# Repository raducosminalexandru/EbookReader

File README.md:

# OpenBook - E-book Reader Open-Source

In cadrul proiectului **OpenBook**, ne propunem sa revoluționam industria cititului digital prin dezvoltarea unui **e-book reader accesibil, eficient si open-source**. 🌍📚

Cu tehnologia de astazi, accesul la informatie este mai rapid ca niciodata, iar **OpenBook** isi propune sa ofere o solutie accesibila tuturor celor care doresc sa citeasca oriunde, oricand, fara a depinde de preturi exorbitante sau de platforme inchise. Suntem o echipa pasionata si inovativa, iar rolul nostru in acest proiect este sa creem un dispozitiv care sa ofere o experienta de citire excelenta si sa fie disponibil pentru toti utilizatorii, fara bariere. 💡

**OpenBook** este un e-book reader care va permite cititorilor sa acceseze si sa citeasca carti digitale intr-un mod simplu si eficient. Acesta ofera o solutie economica si open-source, ceea ce inseamna ca orice persoana va putea sa-l foloseasca, personalizeze sau imbunatateasca, fara restrictii legate de software sau costuri ridicate.

## Cum functioneaza

Prin utilizarea unor componente hardware eficiente si un software open-source, **OpenBook** va oferi o experienta de citire fluida, cu un design simplu si intuitiv. Acesta va suporta formate de carti populare si va fi usor de utilizat, chiar si pentru utilizatorii care nu sunt familiarizati cu tehnologia.

Prin intermediul acestui dispozitiv, punem bazele unui produs care va oferi cititorilor libertatea de a se bucura de carti digitale intr-un mod accesibil si fara compromisuri in ceea ce priveste performanta si functionalitatea.

## Bill of Materials (BOM) - varianta succinta a fisierului BOM

| Componenta               | Link si Datasheet                                                                                           |
|--------------------------|-------------------------------------------------------------------------------------------------------------|
| **ESP32-C6-WROOM-1-N8**   | [Mouser](https://eu.mouser.com/ProductDetail/Espressif-Systems/ESP32-C6-WROOM-1-N8?qs=8Wlm6%252BaMh8ST02Gmwp74cw%3D%3D) |
| **W25Q512JVEIQ**               | [Mouser](https://eu.mouser.com/ProductDetail/Winbond/W25Q512JVEIQ?qs=l7cgNqFNU1jw6svr3at6tA%3D%3D)                                             |
| **DS3231SN#**       | [Mouser](https://www.mouser.ro/ProductDetail/100uF-Capacitor](https://eu.mouser.com/ProductDetail/Analog-Devices-Maxim-Integrated/DS3231SN?qs=1eQvB6Dk1vhUlr8%2FOrV0Fw%3D%3D))                                         |
| **FH34SRJ-24S-0.5SH** | [Mouser](https://www.mouser.ro/ProductDetail/Atmel/ATMEGA328P](https://eu.mouser.com/ProductDetail/Hirose-Connector/FH34SRJ-24S-0.5SH50?qs=iyLo5FA4poC8fzWlavnA7A%3D%3D))                                     |
| **USB4110-GF-A** | [Mouser](https://www.mouser.ro/ProductDetail/Atmel/ATMEGA328P](https://eu.mouser.com/ProductDetail/Hirose-Connector/FH34SRJ-24S-0.5SH50?qs=iyLo5FA4poC8fzWlavnA7A%3D%3D)](https://eu.mouser.com/ProductDetail/GCT/USB4110-GF-A?qs=KUoIvG%2F9IlYiZvIXQjyJeA%3D%3D))                                     |
| **BME680** | [Mouser](https://www.mouser.ro/ProductDetail/Atmel/ATMEGA328P](https://eu.mouser.com/ProductDetail/Hirose-Connector/FH34SRJ-24S-0.5SH50?qs=iyLo5FA4poC8fzWlavnA7A%3D%3D)](https://eu.mouser.com/ProductDetail/GCT/USB4110-GF-A?qs=KUoIvG%2F9IlYiZvIXQjyJeA%3D%3D)](https://eu.mouser.com/ProductDetail/Bosch-Sensortec/BME680?qs=v271MhAjFHjo0yA%2FC4OnDQ%3D%3D))                                     |
| **XC6220A331MR-G** | [Mouser](https://eu.mouser.com/ProductDetail/Torex-Semiconductor/XC6220A331MR-G?qs=AsjdqWjXhJ8ZSWznL1J0gg%3D%3D)                                     |
| **USBLC6-2SC6Y** | [Mouser](https://ro.mouser.com/ProductDetail/STMicroelectronics/USBLC6-2SC6Y?qs=gNDSiZmRJS%2FOgDexvXkdow%3D%3D&_gl=1*hyv6ey*_ga*MTY0NzAzMzgwNi4xNzQyMDMzODgx*_ga_15W4STQT4T*MTc0MzA3NjI1Ny40LjEuMTc0MzA3NjMxMC43LjAuMA)                                     |
| **BD5229G-TR** | [Mouser](https://ro.mouser.com/ProductDetail/ROHM-Semiconductor/BD5229G-TR?qs=4kLU8WoGk0vvnhrrYwdszw%3D%3D)                                     |
| **MAX17048G+T10** | [Mouser](https://ro.mouser.com/ProductDetail/Analog-Devices-Maxim-Integrated/MAX17048G%2bT10?qs=D7PJwyCwLAoGnnn8jEPRBQ%3D%3D)                                     |
| **W25Q512JVEIQ** | [Mouser](https://ro.mouser.com/ProductDetail/ROHM-Semiconductor/BD5229G-TR?qs=4kLU8WoGk0vvnhrrYwdszw%3D%3D](https://ro.mouser.com/ProductDetail/Winbond/W25Q512JVEIQ?qs=l7cgNqFNU1jw6svr3at6tA%3D%3D))  
| **Qwiic Right Angle** | [Mouser](https://ro.mouser.com/ProductDetail/Adafruit/4208?qs=PzGy0jfpSMtbScLbr0L5dw%3D%3D) |

Urmatoarea imagine prezinta diagrama bloc de interconectare a componentelor, inclusiv tensiunile de alimentare si protocoalele de comunicatie utilizate intre ele. 🔌📡

<div align="center">

</div>

Modelul 3D al PCB-ului poate fi observat si in imaginea urmatoare, ceea ce permite o analiza detaliata a componentei si a configuratiei acestuia. Acest model ofera o perspectiva clara asupra dimensiunilor, plasarii componentelor si a traseelor de pe placa, ajutand la identificarea posibilelor interferente sau probleme de proiectare.

<div align="center">

</div>

Putem vizualiza si traseele mai bine in modelul 3D, ceea ce faciliteaza o analiza mai detaliata a conexiunilor dintre componente. Acest lucru permite identificarea eventualelor probleme legate de lungimea sau latimea traseelor, precum si a eventualelor puncte de coliziune sau interferenta.

<div align="center">

</div>

📐 **Integrarea modelului 3D al display-ului si al bateriei**

Pentru o reprezentare cat mai completa a ansamblului final, au fost incluse in proiect si modelele 3D ale display-ului si ale bateriei. Aceasta decizie a avut un rol esential in etapa de validare a designului, permitand o evaluare vizuala si functionala a intregului sistem, direct in mediul 3D.

Prin integrarea acestor componente, a fost posibila:
- ✅ **Verificarea compatibilitatii dimensionale** – Asigurarea ca fiecare componenta are un spatiu adecvat in interiorul carcasei, fara suprapuneri sau conflicte mecanice.
- 🧩 **Optimizarea pozitionarii componentelor** – Plasarea strategica a display-ului si bateriei pentru a facilita accesul, vizibilitatea, distributia greutatii si eficienta termica.
- 🧠 **Identificarea timpurie a potentialelor probleme de spatiu** – Vizualizarea in 3D permite observarea oricaror interferente sau nepotriviri intre PCB, baterie, display si carcasa proiectului.
- 🔧 **Eficientizarea procesului de prototipare** – Un model 3D complet si realist reduce riscul de erori in faza de fabricatie, scurtand ciclurile de testare si ajustare.

Aceasta abordare contribuie direct la cresterea fiabilitatii produsului final, asigurand ca toate componentele nu doar functioneaza impreuna, ci si se potrivesc perfect in structura fizica a dispozitivului.

</div>

<div align="center">

</div>

<div align="center">

</div>

<div align="center">

</div>

### Cerinte de 'Good Practice' respectate de dispozitiv:

✅ Traseele de alimentare (VCC, VUSB, VBUS, 3V3 etc.) sunt rutate folosind width = 0.3mm, semnalele de date cu minimum width de 0.15mm.  
✅ Antena modulului ESP32 este amplasata spre exteriorul PCB-ului si PCB-ul trebuie sa fie decupat sub antena.  
✅ Verificare ERC si DRC.  
✅ Condensatoarele de decuplare (100nF) sunt amplasate cat mai aproape de pinii de alimentare ai diferitelor module si circuite integrate.  
✅ Suprafata PCB-ului de sub antena modulului ESP32 a fost decupata pentru a crea cat mai putine interferente cu semnalul radio.  
✅ Planuri de masa situate pe ambele nivele (TOP, BOTTOM).  
✅ Antena modulului ESP32 este amplasata spre exteriorul PCB-ului si PCB-ul este decupat sub antena.  
✅ S-a aplicat 'Via Stitching' intre cele doua planuri de masa, in special in preajma modulului ESP32, precum si in jurul componentelor principale.
✅ Placa are grosimea de 1mm, lucru ce permite introducerea in carcasa si pozitionarea corecta a mufelor.
✅ Vias-uri legate de masa au fost aplicate in toate zonele in care nu se facea 'Pour'.
✅ Valorile rezistentelor si condensatoarelor au fost sterse din 'Board' de pe layer-ul 'Silkscreen' pentru a permite o lizibilitate mai buna.
✅ Footprint-urile anumitor componente au fost schimbate prin modificarea marimilor unor pini, permitand traseele de putere sa se lege la ele, acestea fiind mai groase.
✅ Nu exista unghiuri drepte in cadrul rutarii pe placa.

### Erori acceptate pe dispozitiv:
✅Erorile 'Board Outline Clearance', conform cerintelor impuse.

### 🌐 Surse auxiliare utilizate pentru modele 3D

## Surse externe pentru modelarea 3D a ansamblului

Pentru a completa designul 3D al placii si a asigura o reprezentare cat mai fidela a ansamblului, au fost utilizate urmatoarele surse externe:

🔍 **Component Search Engine**  
Aceasta platforma a fost principalul instrument folosit pentru importarea modelelor 3D ale componentelor electronice standard. A oferit o integrare rapida si precisa cu software-ul de proiectare, facilitand plasarea corecta a componentelor in layout-ul 3D.

🟢 **Farnell**  
Modelele 3D ale butoanelor nu erau disponibile in Component Search Engine, asa ca s-a apelat la biblioteca pusa la dispozitie de Farnell. Aceasta ofera fisiere 3D compatibile si bine detaliate, utile pentru verificarea dimensiunilor fizice si a spatiului ocupat pe placa.

📦 **GrabCAD**  
Modelul 3D al Solder Jumper-ului (SJ) a fost descarcat de pe GrabCAD, o platforma colaborativa care pune la dispozitie o varietate larga de modele CAD. A fost ales un model potrivit, care a fost ulterior ajustat pentru a corespunde dimensiunilor reale folosite in proiect.

# Pinii ESP32 C6 folositi

Se poate vizualiza modul de conectare al componentelor in raport cu ESP32 C6. Se poate observa clar cum acesta poate fi atat 'Master', cat si 'Slave', lucru ce permite comunicatia SPI.

## 1. SD Card
- **CLK** → GPIO6  
- **CMD** → GPIO7  
- **DATA0** → GPIO8  
- **DATA1** → GPIO9  
- **DATA2** → GPIO10  
- **DATA3** → GPIO11  

## 2. Ecran E-Paper
Comunicare prin SPI și GPIO-uri adiționale:
- **MOSI** → GPIO4  
- **SCK** → GPIO5  
- **DC** → GPIO18  
- **CS** → GPIO17  
- **BUSY** → GPIO16  
- **RESET** → GPIO15  

## 3. Memorie NOR Flash 64MB (W25Q512JV)
Comunicare prin SPI:
- **MOSI** → GPIO4  
- **MISO** → GPIO3  
- **CLK** → GPIO5  
- **CS** → GPIO2  

## 4. Senzor de mediu BME688 (I2C)
- **SCL** → GPIO20  
- **SDA** → GPIO19  

## 5. RTC DS3231SN (I2C)
- **SCL** → GPIO20  
- **SDA** → GPIO19  

## 6. Qwiic / Stemma QT (I2C)
- **SCL** → GPIO20  
- **SDA** → GPIO19  

## 7. Indicator nivel baterie (MAX17048G+T10) (I2C)
- **SCL** → GPIO20  
- **SDA** → GPIO19  

## 8. Buton de Reset și Boot
- **Reset** → GPIO0  
- **Boot** → GPIO1

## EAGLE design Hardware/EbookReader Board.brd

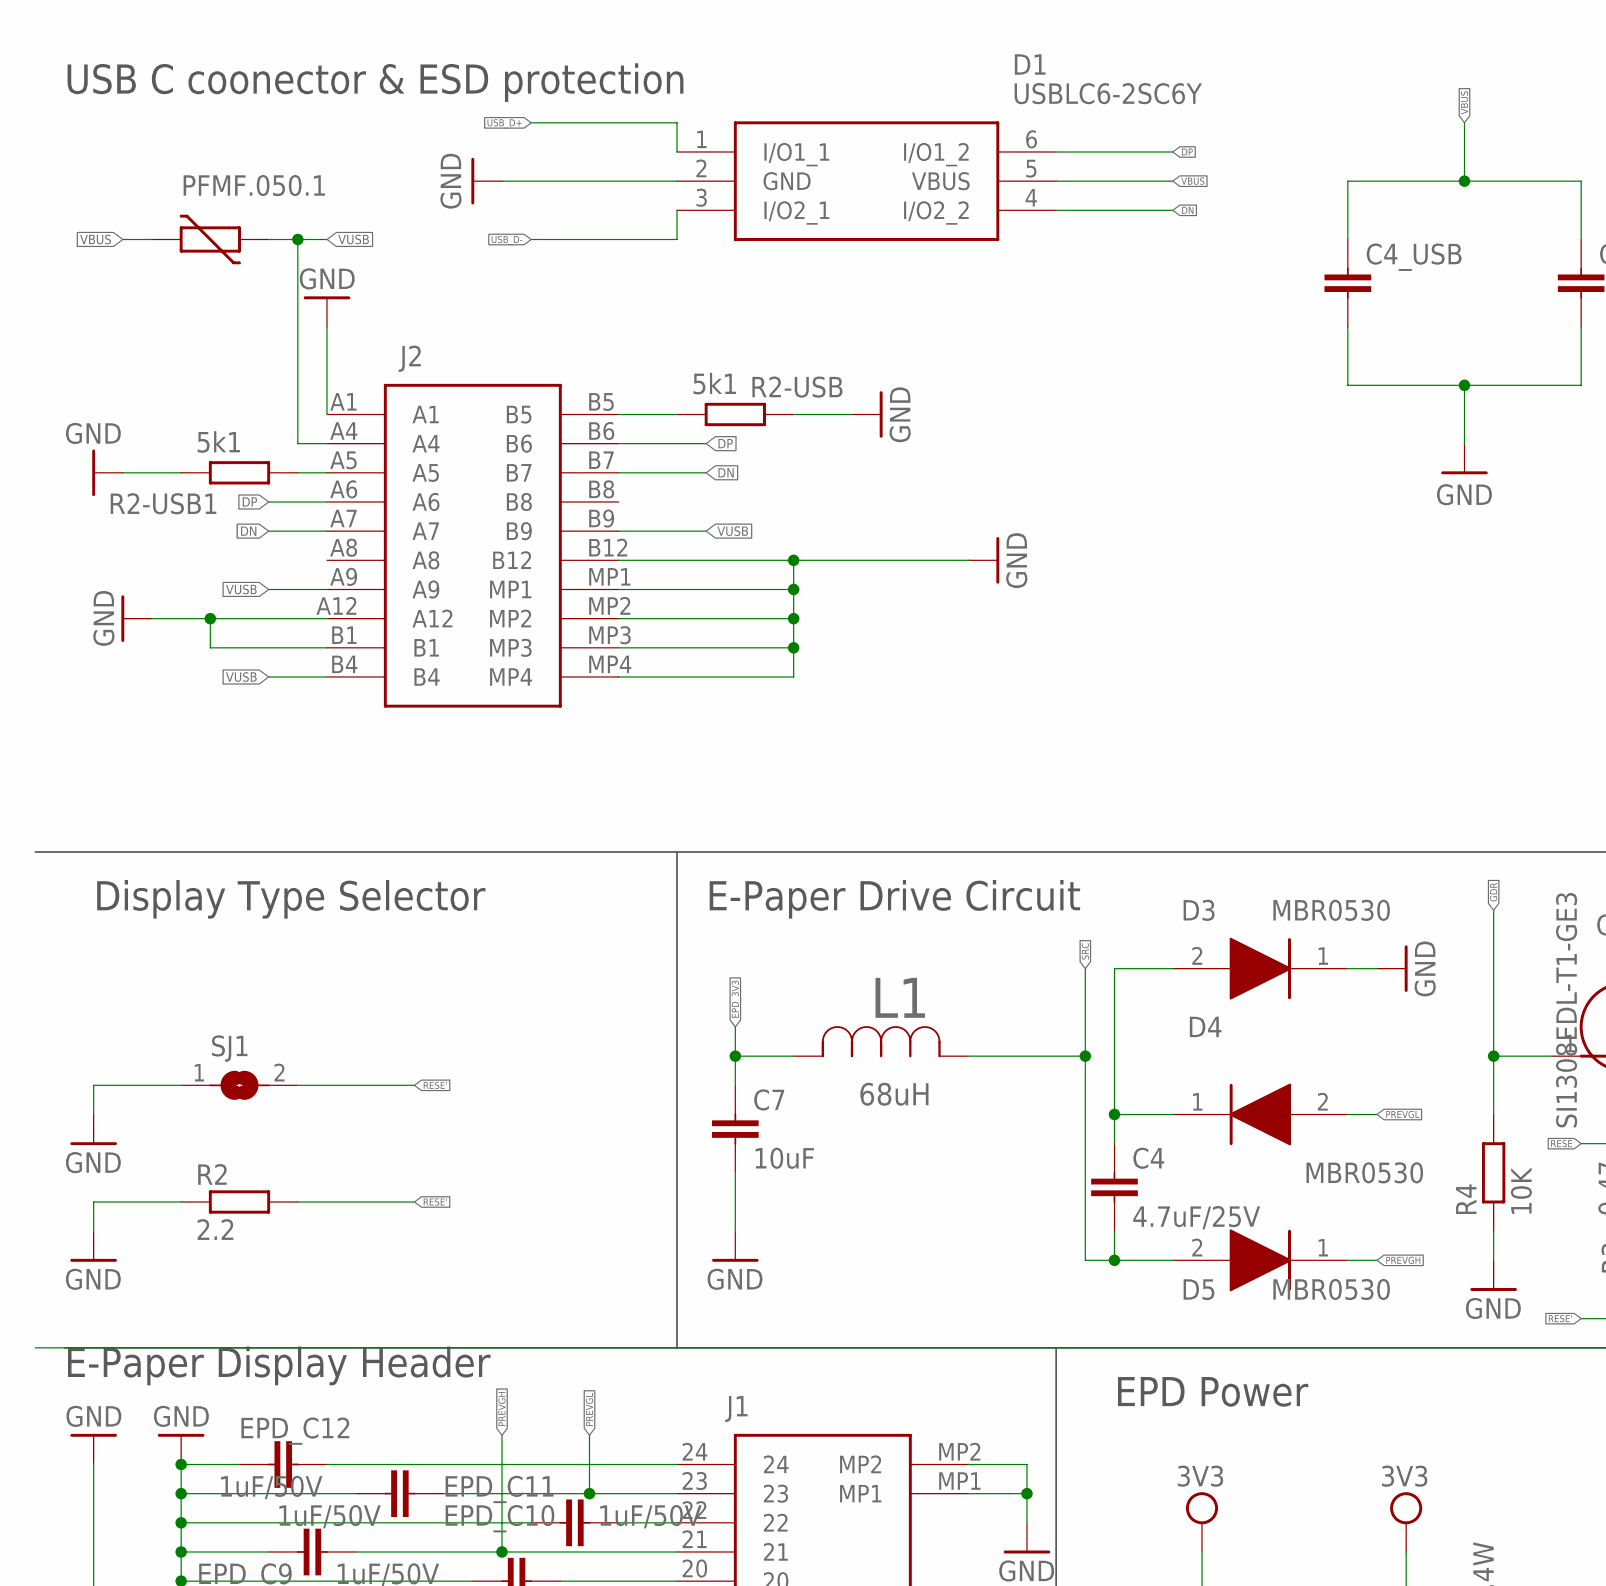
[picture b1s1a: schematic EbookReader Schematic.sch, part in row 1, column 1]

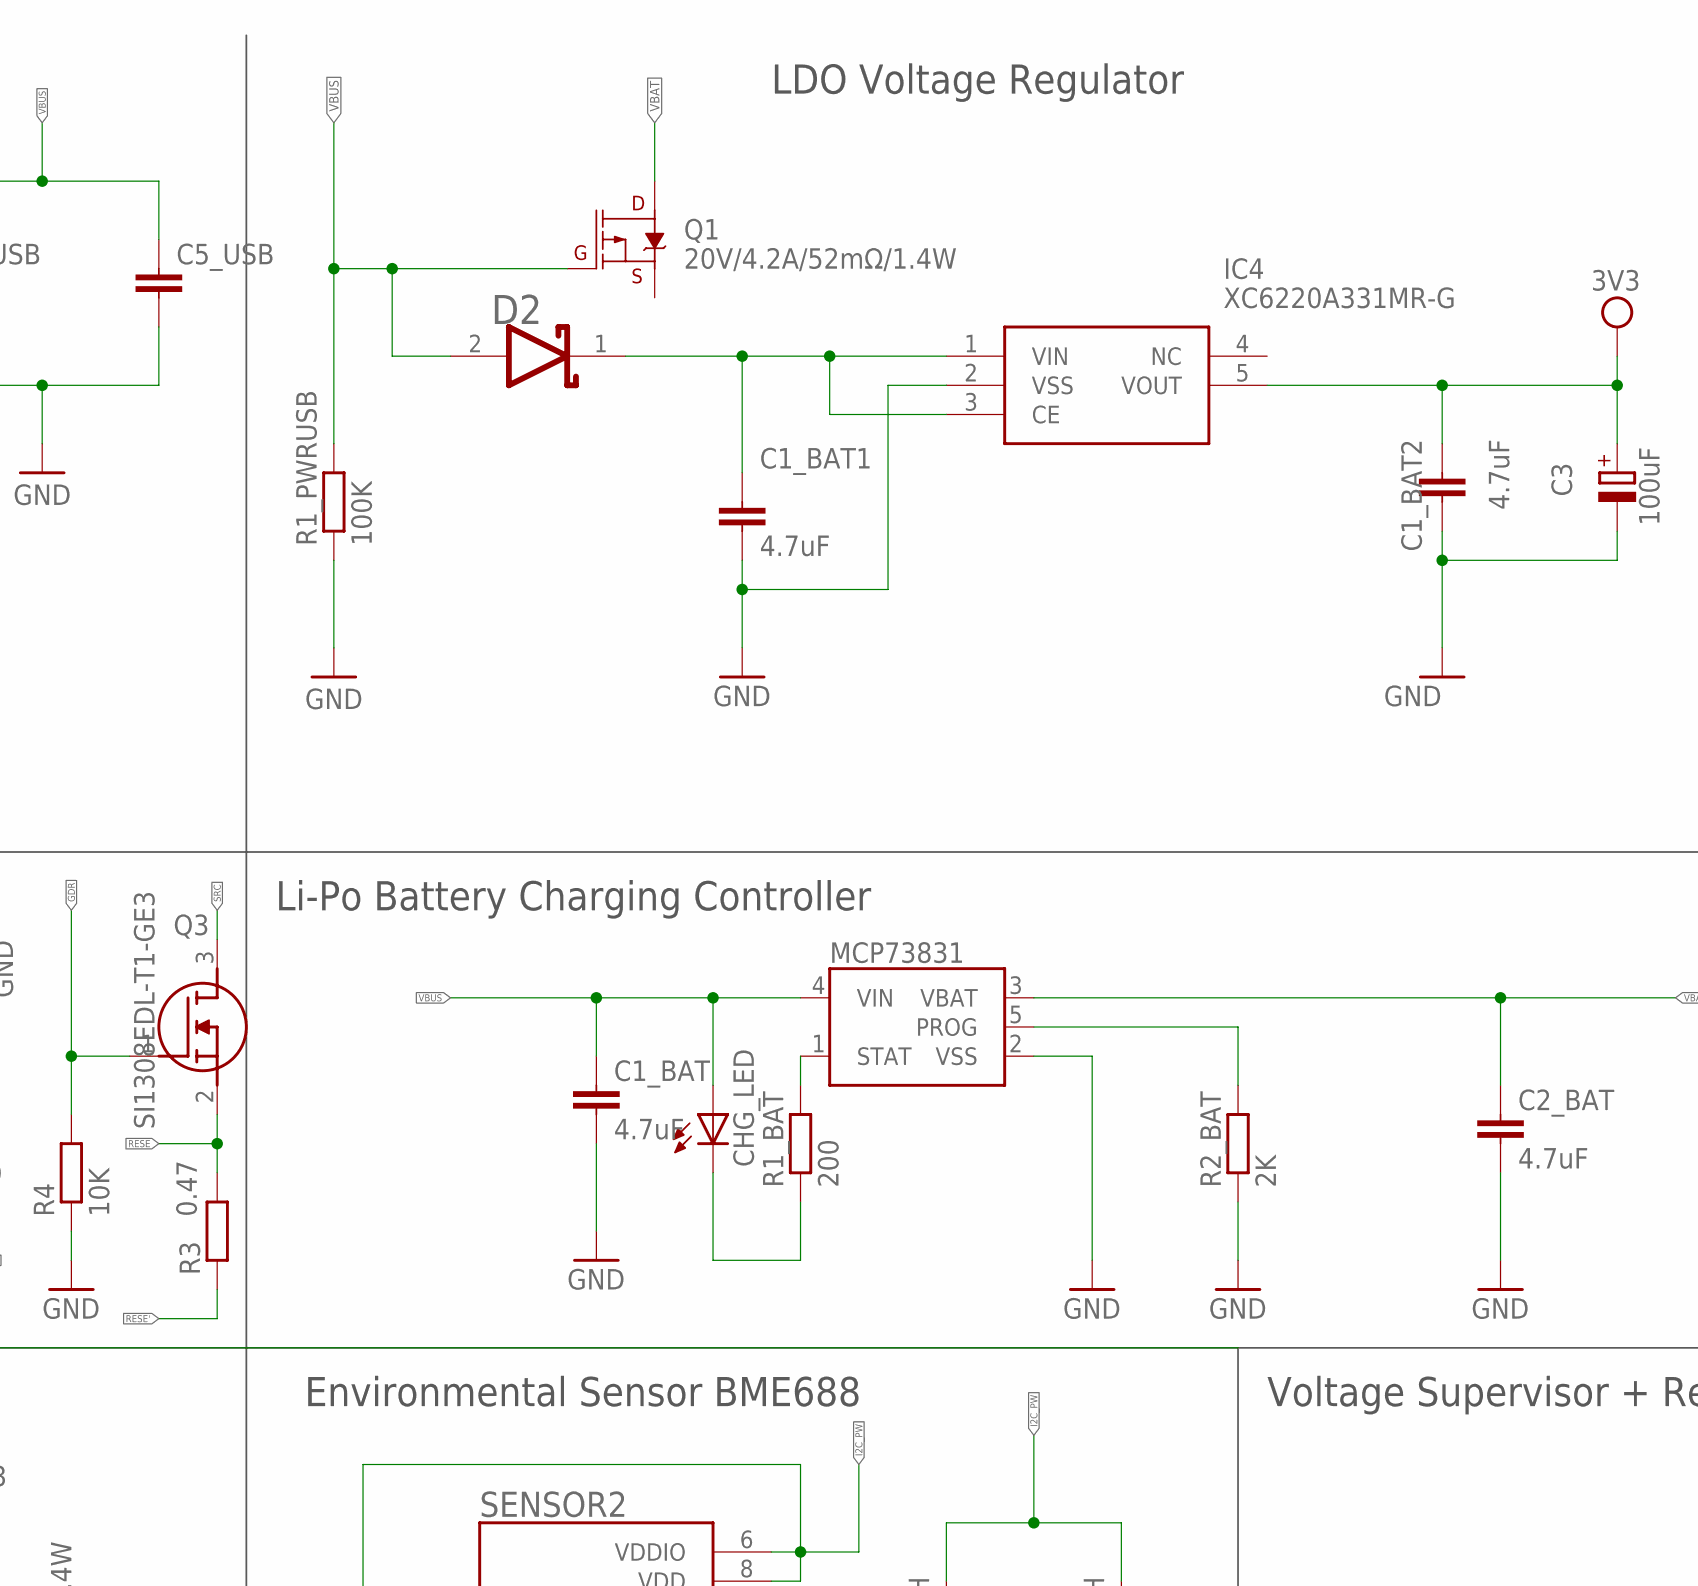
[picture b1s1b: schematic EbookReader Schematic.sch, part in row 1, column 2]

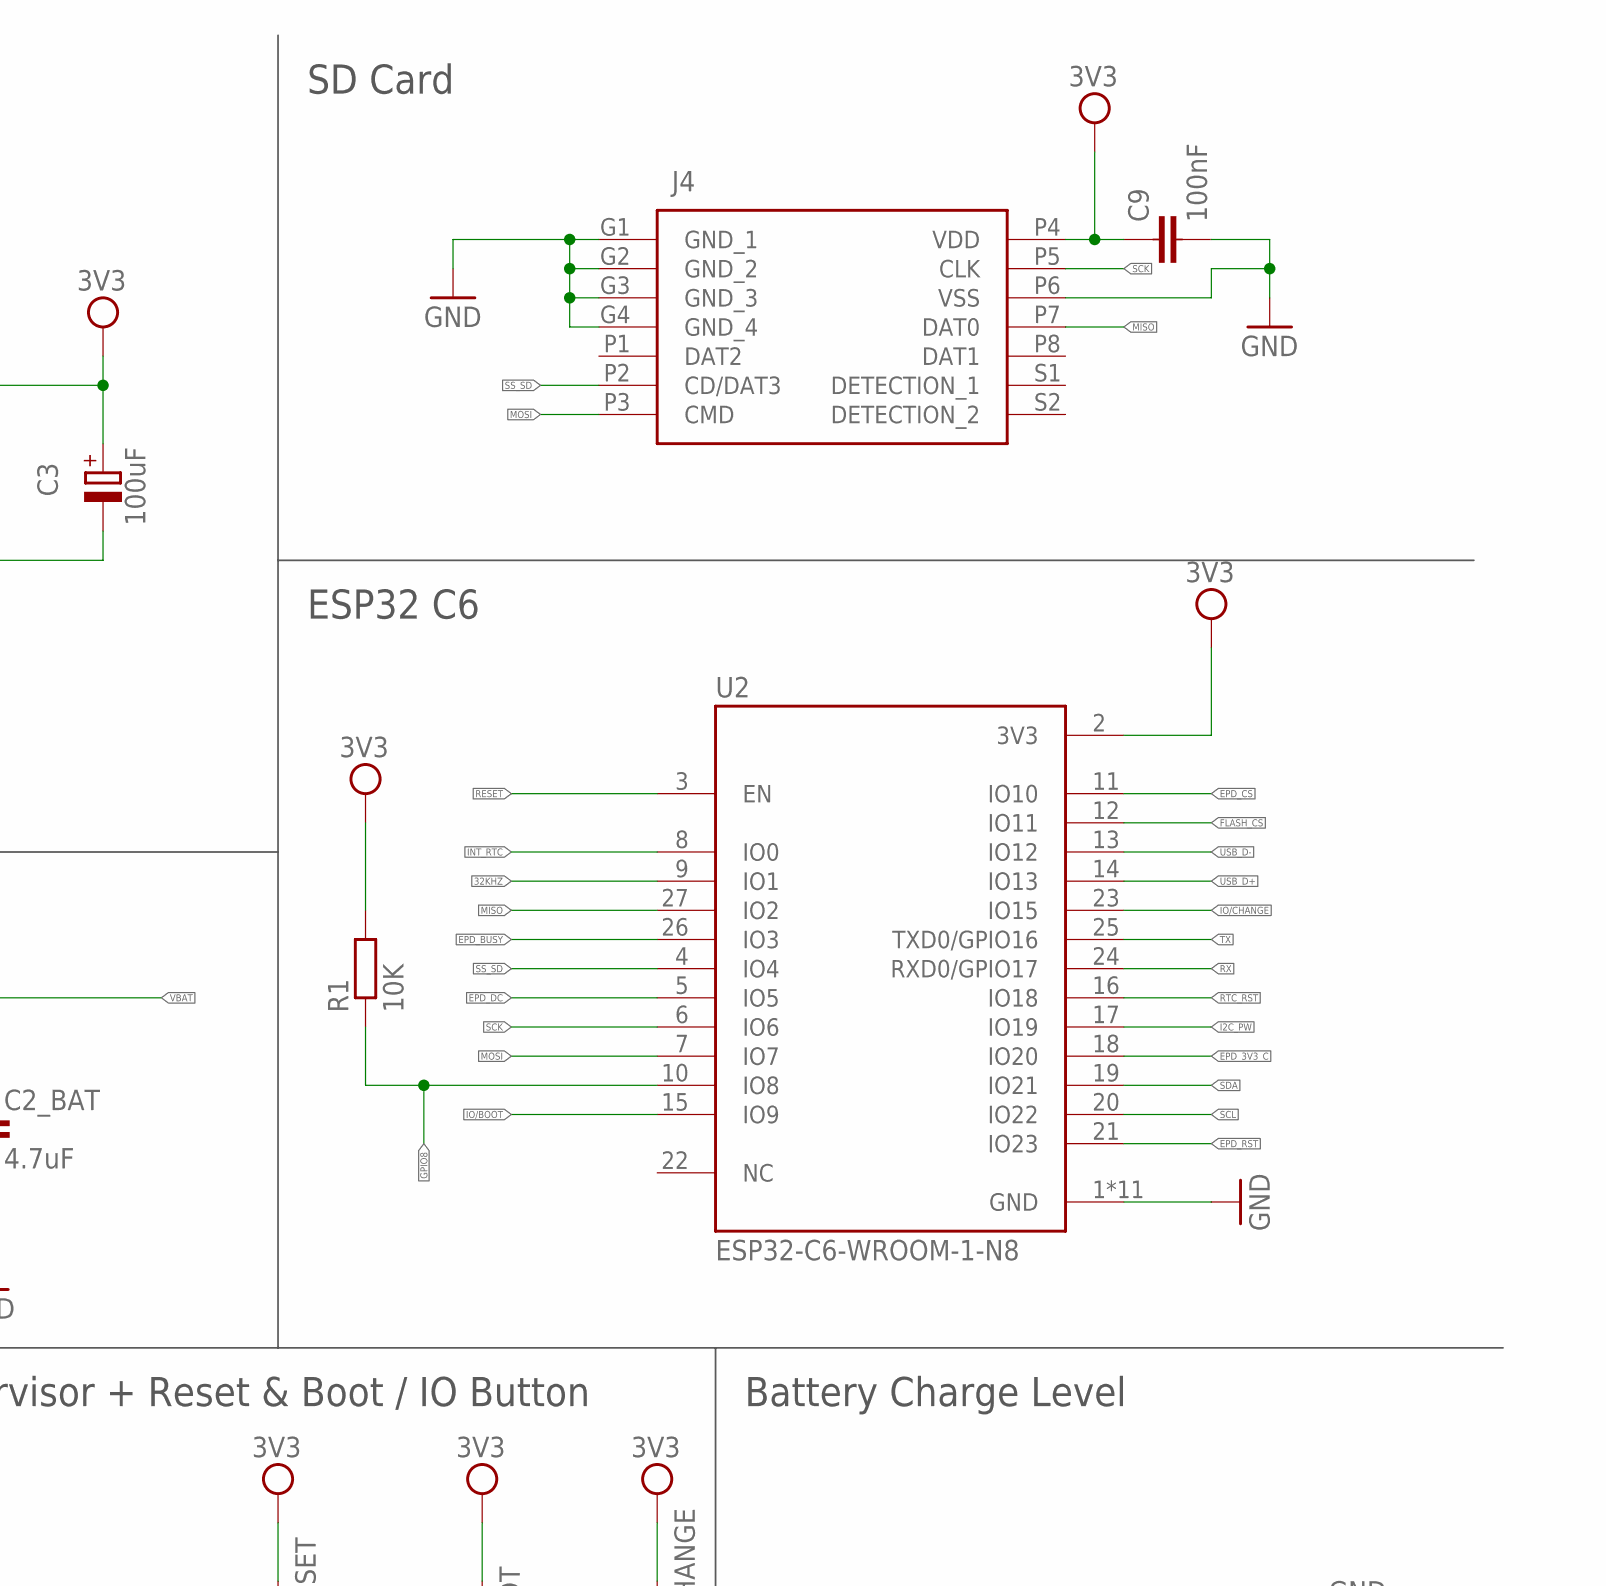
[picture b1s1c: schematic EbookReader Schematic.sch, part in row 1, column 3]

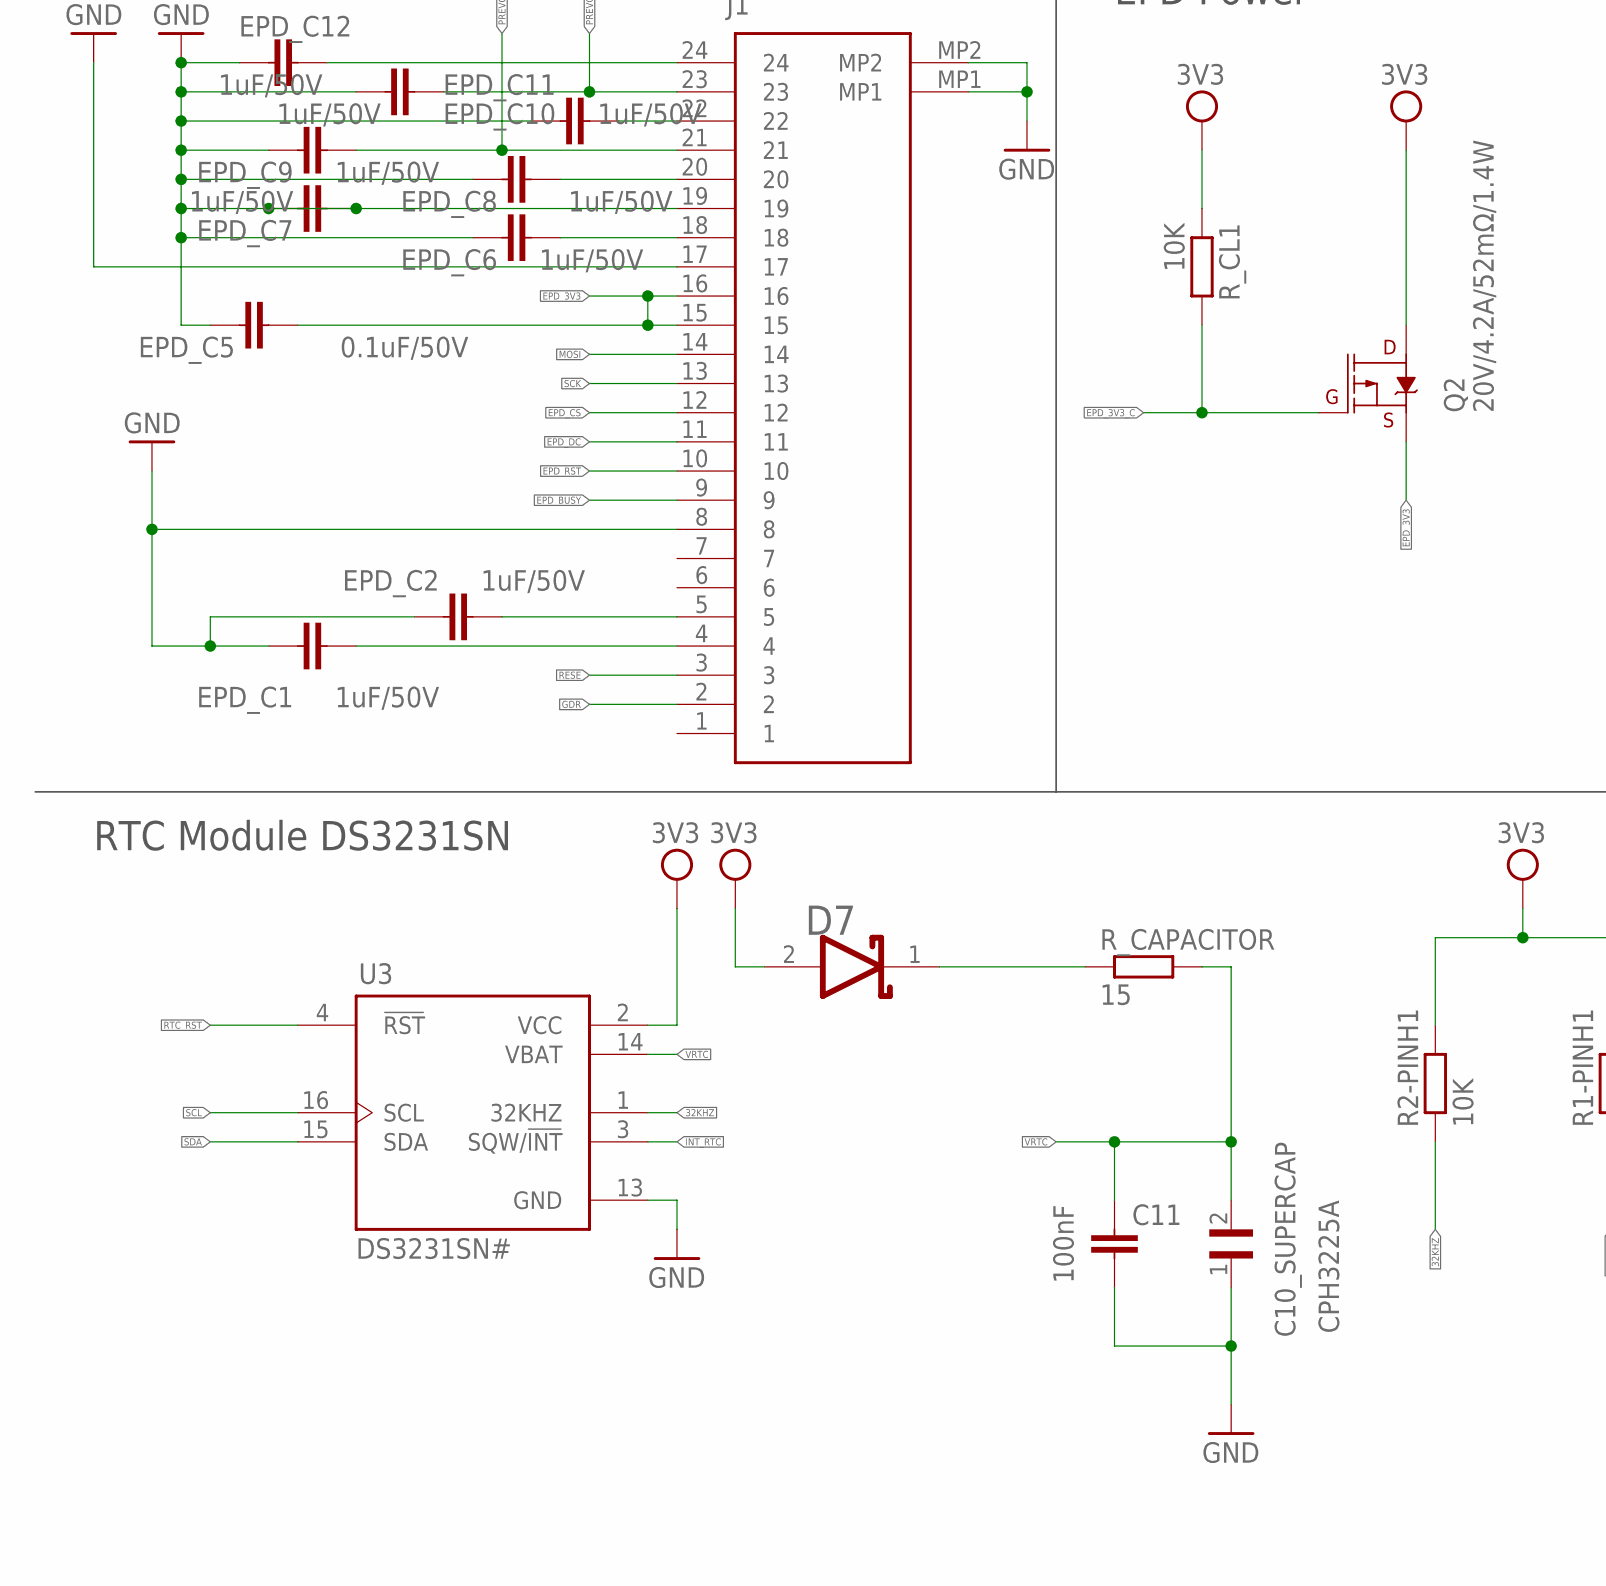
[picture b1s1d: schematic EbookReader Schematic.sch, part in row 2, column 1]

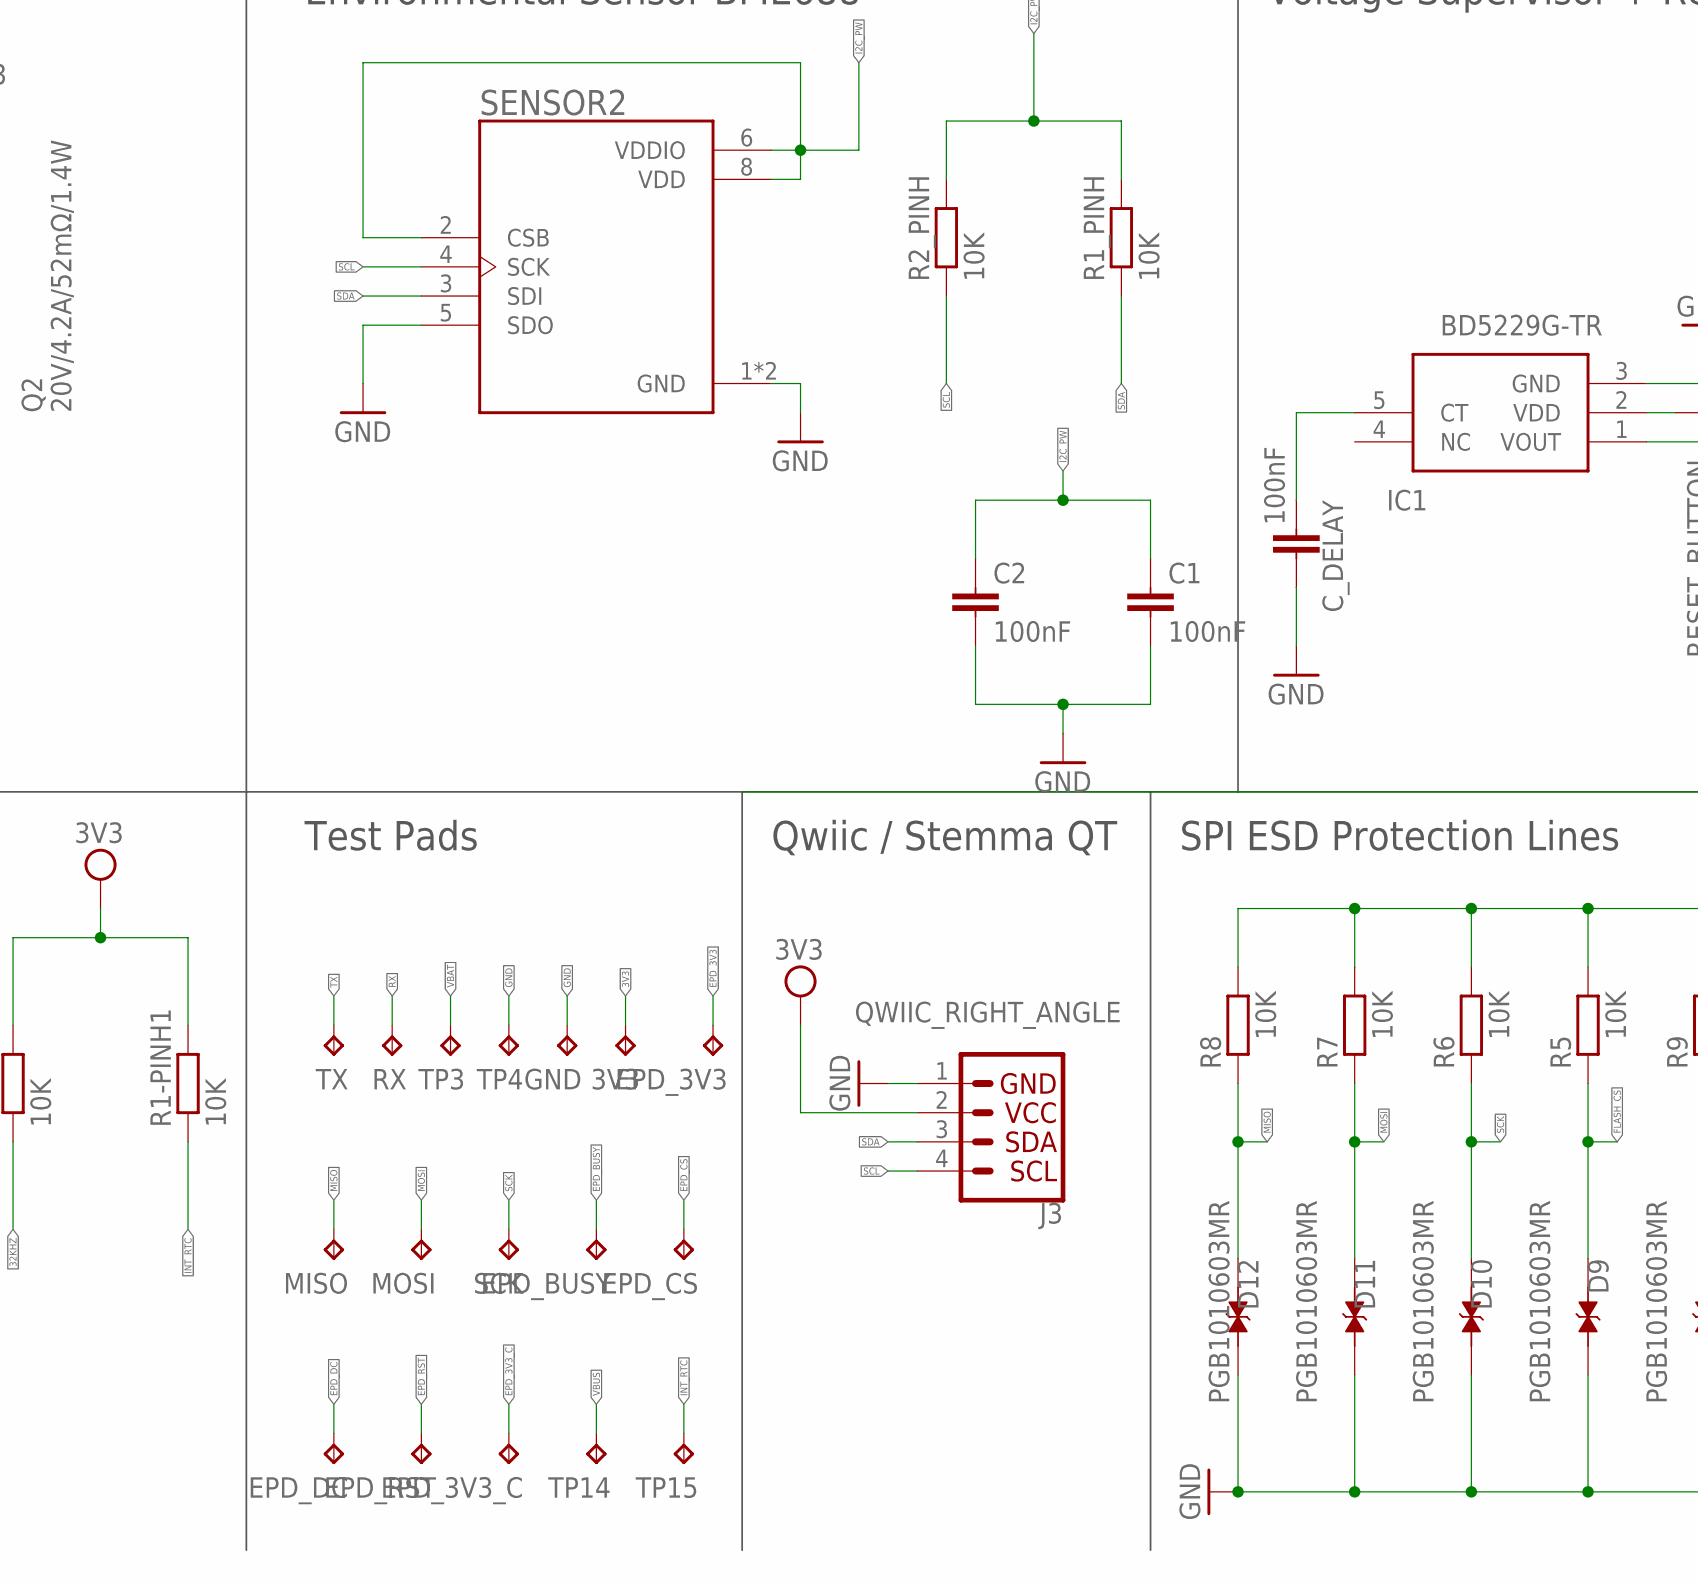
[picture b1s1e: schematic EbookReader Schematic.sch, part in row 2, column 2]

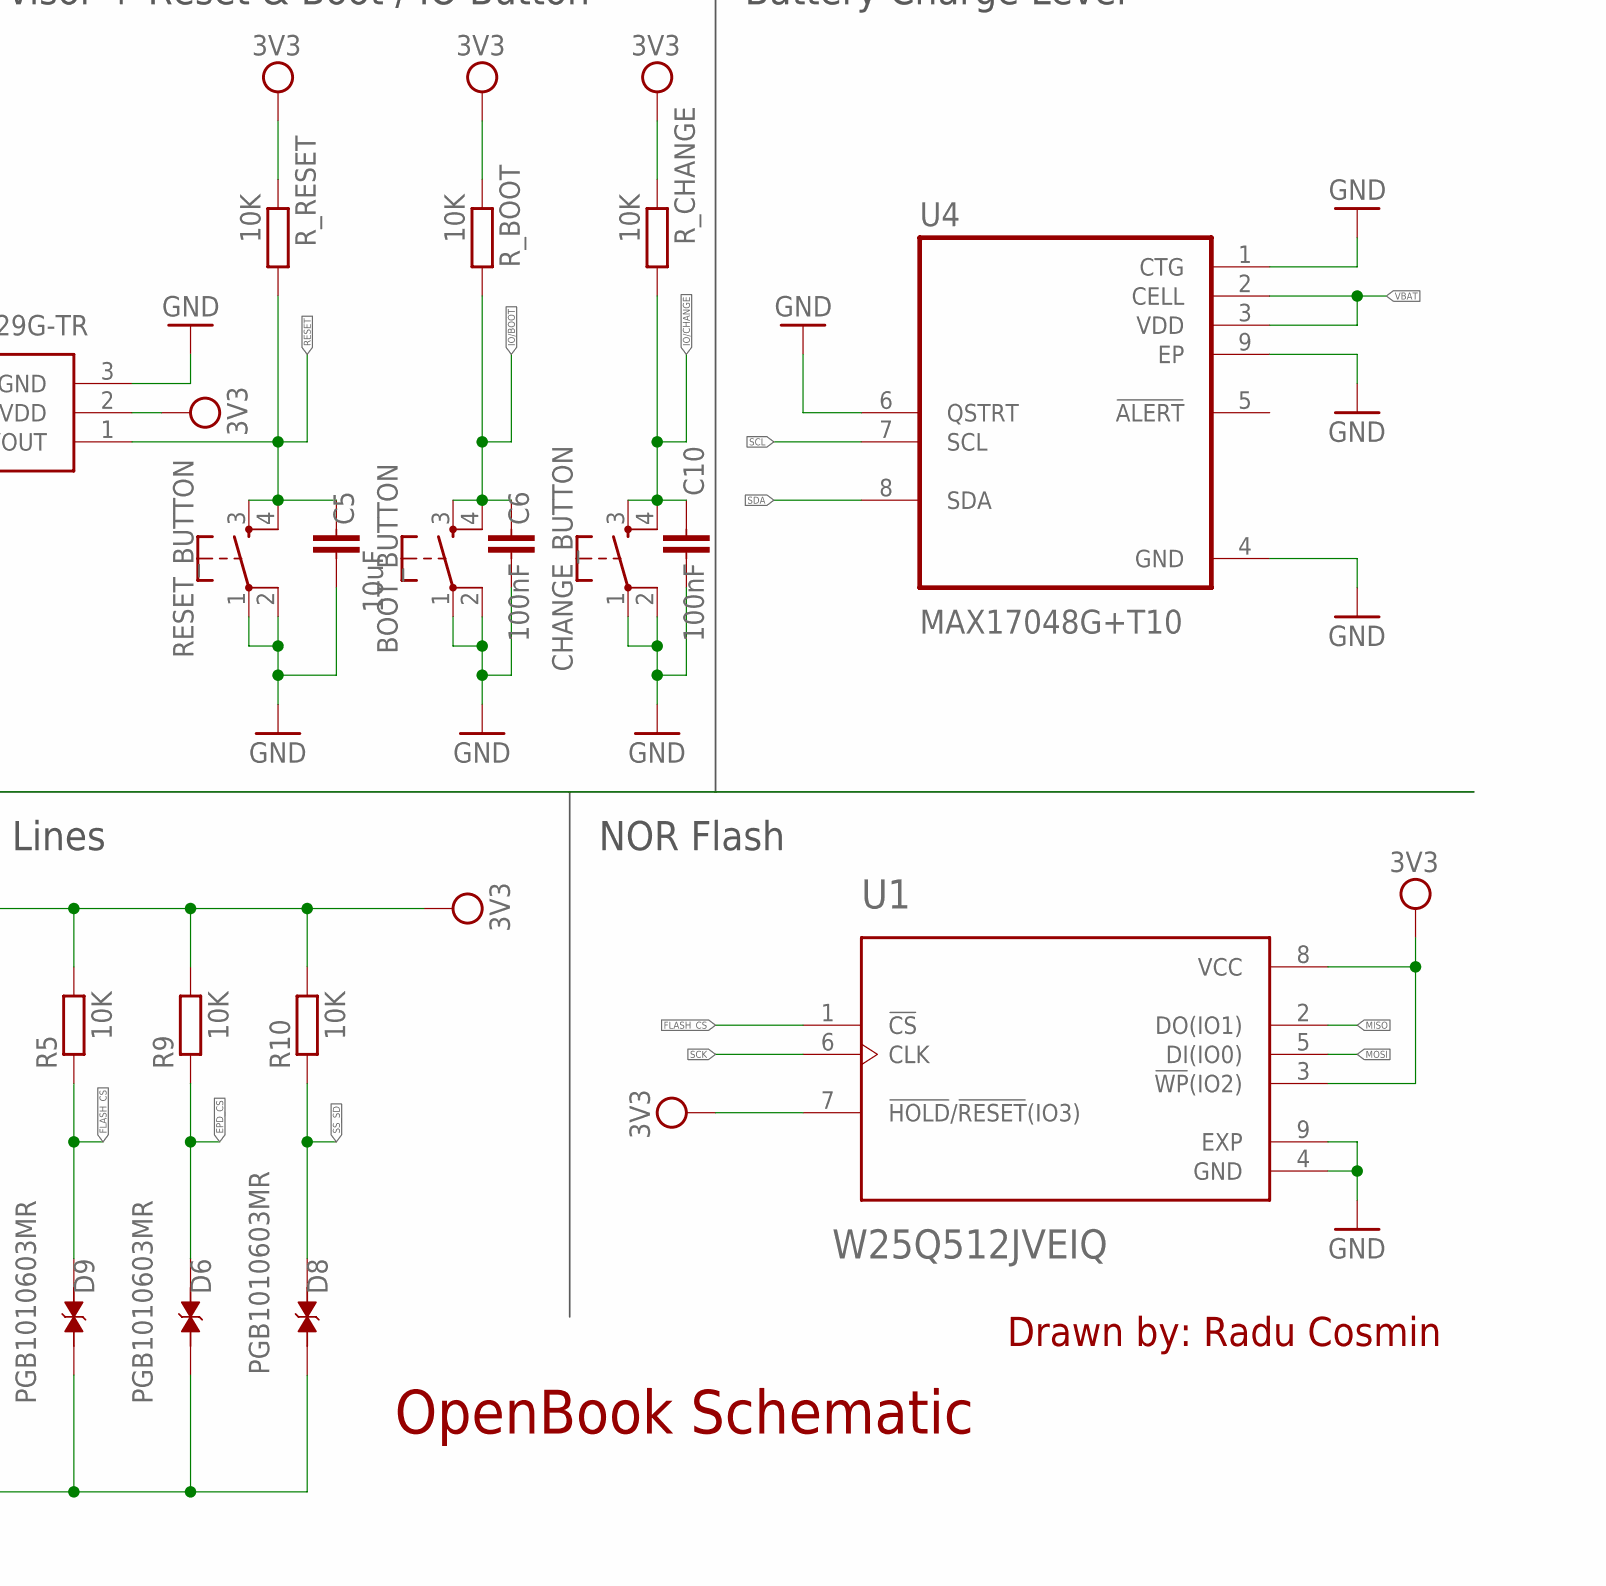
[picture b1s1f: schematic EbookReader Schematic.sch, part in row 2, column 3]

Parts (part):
3V3: TPTP20R; TP20R
BOOT_BUTTON: BUTTON_CUSYOMV1; MYBUTTON
C1, C2, C6, C9, C10, C11: 100nF; ESP32_WROVER_EAGLE-LTSPICE_C0402
C1_BAT, C1_BAT1, C1_BAT2, C2_BAT: 4.7uF; ESP32_WROVER_EAGLE-LTSPICE_C0402
C3: 100uF; RCL_CT3528
C4: 4.7uF/25V; ESP32_WROVER_EAGLE-LTSPICE_C0402
C4_USB, C5_USB: ESP32_WROVER_EAGLE-LTSPICE_CC0402; ESP32_WROVER_EAGLE-LTSPICE_C0402
C5, C7: 10uF; ESP32_WROVER_EAGLE-LTSPICE_C0402
C10_SUPERCAP: CPH3225A; CAPCP3225X100N
CHANGE_BUTTON: BUTTON_CUSYOMV1; MYBUTTON
CHG_LED: ADAFRUIT_LEDCHIP-LED0603; ADAFRUIT_CHIP-LED0603
C_DELAY: 100nF; ESP32_WROVER_EAGLE-LTSPICE_C0402
D1: USBLC6-2SC6Y; SOT95P280X145-6N
D2, D7: ESP32_WROVER_AVX---SD0805S020S1R0_AVX_SD0805S020S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; ESP32_WROVER_AVX---SD0805S020S1R0_AVX_SD0805S020S1R0_0
D3, D4, D5: MBR0530; SOD3716X135N
D6, D8, D9, D10, D11, D12: PGB1010603MR; DIOC1608X36N
EPD_3V3, EPD_3V3_C: TPTP20R; TP20R
EPD_BUSY: TPTP20R; TP20R
EPD_C1, EPD_C2, EPD_C6, EPD_C7, EPD_C8, EPD_C9, EPD_C10, EPD_C11, EPD_C12: 1uF/50V; ESP32_WROVER_EAGLE-LTSPICE_C0402
EPD_C5: 0.1uF/50V; ESP32_WROVER_EAGLE-LTSPICE_C0402
EPD_CS: TPTP20R; TP20R
EPD_DC: TPTP20R; TP20R
EPD_RST: TPTP20R; TP20R
GND: TPTP20R; TP20R
IC1: BD5229G-TR; SOT95P280X125-5N
IC4: XC6220A331MR-G; SOT95P280X120-5N
J1: FH34SRJ-24S-0.5SH_99_; FH34SRJ24S05SH99
J2: SAMACSYS_PARTS_USB4110-GF-A; SAMACSYS_PARTS_USB4110GFA
J3: QWIIC_RIGHT_ANGLE; JST04_1MM_RA
J4: 112A-TAAR-R03_ATTEND; 112ATAARR03ATTEND
L1: 68uH; IND_4828-WE-TPC_WRE
MCP73831: ESP32_WROVER_SPARKFUN-IC-POWER_MCP73831; ESP32_WROVER_SPARKFUN-IC-POWER_SOT23-5
MISO: TPTP20R; TP20R
MOSI: TPTP20R; TP20R
PFMF.050.1: ESP32C6_VARISTORCN1812; ESP32C6_VARISTOR_CT/CN1812
Q1, Q2: 20V/4.2A/52mΩ/1.4W; ESP32_WROVER_SPARKFUN-DISCRETESEMI_SOT23-3
Q3: SI1308EDL-T1-GE3; SOT65P210X110-3N
R1, R1-PINH1, R1_PINH, R2-PINH1, R2_PINH, R4, R5, R6, R7, R8, R9, R10: 10K; ESP32_WROVER_EAGLE-LTSPICE_R0402
R1_BAT: 200; ESP32_WROVER_EAGLE-LTSPICE_R0402
R1_PWRUSB: 100K; ESP32_WROVER_EAGLE-LTSPICE_R0402
R2: 2.2; ESP32_WROVER_EAGLE-LTSPICE_R0402
R2-USB, R2-USB1: 5k1; ESP32_WROVER_EAGLE-LTSPICE_R0402
R2_BAT: 2K; ESP32_WROVER_EAGLE-LTSPICE_R0402
R3: 0.47; ESP32_WROVER_EAGLE-LTSPICE_R0402
RESET_BUTTON: BUTTON_CUSYOMV1; MYBUTTON
RX: TPTP20R; TP20R
R_BOOT: 10K; ESP32_WROVER_EAGLE-LTSPICE_R0402
R_CAPACITOR: 15; ESP32_WROVER_EAGLE-LTSPICE_R0402
R_CHANGE: 10K; ESP32_WROVER_EAGLE-LTSPICE_R0402
R_CL1: 10K; ESP32_WROVER_EAGLE-LTSPICE_R0402
R_RESET: 10K; ESP32_WROVER_EAGLE-LTSPICE_R0402
SCK: TPTP20R; TP20R
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
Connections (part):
3V3: 3V3.TP, C1_BAT2.1, C3.+, C9.1, D7.2 (ANODE), IC1.2 (VDD), IC4.5 (VOUT), J3.2, J4.P4 (VDD), Q2.3 (D), R1.2, R1-PINH1.2, R2-PINH1.2, R5.2, R6.2, R7.2, R8.2, R9.2, R10.2, R_BOOT.1, R_CHANGE.1, R_CL1.1, R_RESET.1, U1.3 (!WP!(IO2)), U1.7 (!HOLD!/!RESET!(IO3)), U1.8 (VCC), U2.2 (3V3), U3.2 (VCC)
32KHZ: R2-PINH1.1, U2.9 (IO1), U3.1 (32KHZ)
DN: D1.4 (I/O2_2), J2.A7, J2.B7
DP: D1.6 (I/O1_2), J2.A6, J2.B6
EPD_3V3: C7.1, EPD_3V3.TP, EPD_C5.2, J1.15, J1.16, L1.2, Q2.2 (S)
EPD_3V3_C: EPD_3V3_C.TP, Q2.1 (G), R_CL1.2, U2.18 (IO20)
EPD_BUSY: EPD_BUSY.TP, J1.9, U2.26 (IO3)
EPD_CS: D6.1, EPD_CS.TP, J1.12, R9.1, U2.11 (IO10)
EPD_DC: EPD_DC.TP, J1.11, U2.5 (IO5)
EPD_RST: EPD_RST.TP, J1.10, U2.21 (IO23)
FLASH_CS: D9.1, R5.1, U1.1 (!CS), U2.12 (IO11)
GDR: J1.2, Q3.1 (G), R4.2
GND: BOOT_BUTTON.1, BOOT_BUTTON.2, C1.2, C1_BAT.2, C1_BAT1.2, C1_BAT2.2, C2.2, C2_BAT.2, C3.-, C4_USB.2, C5.2, C5_USB.2, C6.2, C7.2, C9.2, C10.2, C10_SUPERCAP.1, C11.2, CHANGE_BUTTON.1, CHANGE_BUTTON.2, C_DELAY.2, D1.2 (GND), D3.1 (K), D6.2, D8.2, D9.2, D10.2, D11.2, D12.2, EPD_C1.1, EPD_C2.1, EPD_C5.1, EPD_C6.1, EPD_C7.1, EPD_C7.2, EPD_C8.1, EPD_C9.1, EPD_C10.1, EPD_C11.1, EPD_C12.1, GND.TP, IC1.3 (GND), IC4.2 (VSS), J1.8, J1.17, J1.19, J1.MP1, J1.MP2, J2.A1, J2.A12, J2.B1, J2.B12, J2.MP1, J2.MP2, J2.MP3, J2.MP4, J3.1, J4.G1 (GND_1), J4.G2 (GND_2), J4.G3 (GND_3), J4.G4 (GND_4), J4.P6 (VSS), MCP73831.2 (VSS), R1_PWRUSB.1, R2.1, R2-USB.2, R2-USB1.1, R2_BAT.1, R4.1, RESET_BUTTON.1, RESET_BUTTON.2, SENSOR2.1 (GND), SENSOR2.5 (SDO), SENSOR2.7 (GND), SJ1.1, TP4.TP, U1.4 (GND), U1.9 (EXP), U2.1 (GND), U2.28 (GND), U2.29_1 (GND), U2.29_2 (GND), U2.29_3 (GND)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
GPIO8: R1.1, U2.10 (IO8)
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
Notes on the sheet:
Drawn by: Radu Cosmin
OpenBook Schematic
USB C coonector & ESD protection
LDO Voltage Regulator
SD Card
Display Type Selector
E-Paper Drive Circuit
Li-Po Battery Charging Controller
ESP32 C6
E-Paper Display Header
EPD Power
Environmental Sensor BME688
Voltage Supervisor + Reset & Boot / IO Button
Battery Charge Level
RTC Module DS3231SN
Test Pads
Qwiic / Stemma QT
SPI ESD Protection Lines
NOR Flash

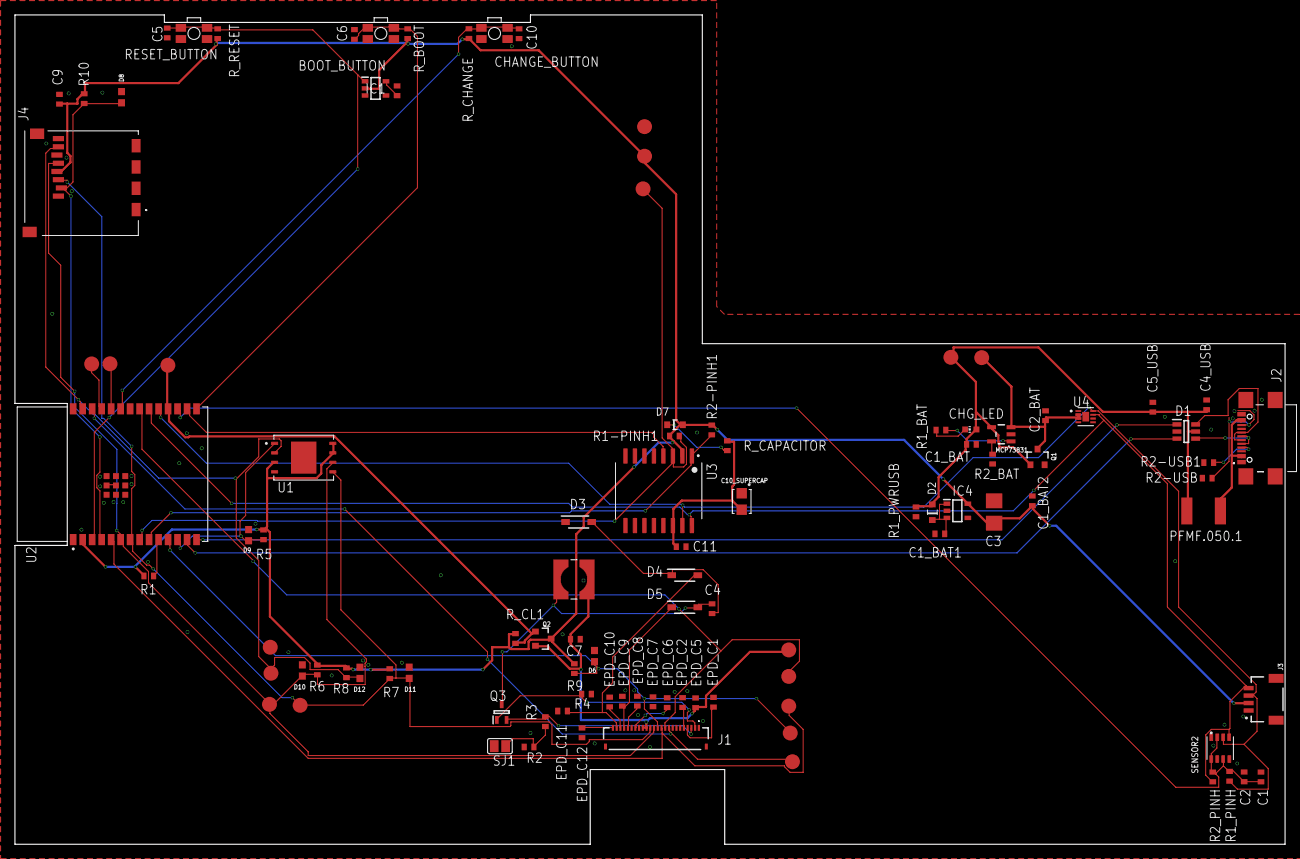
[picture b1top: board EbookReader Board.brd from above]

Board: 2 copper layers, 170.0 x 111.0 mm, 103 parts (0 on the bottom side), 54 nets.

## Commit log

2025-03-25 Adaugare a tuturor fisierelor care constituie dispozitivul EbookReader
2025-03-25 Update README.md
    Adaugare 'Bill of Materials'
2025-03-27 Adaugare diagrama de interconectare
2025-03-28 Adaugare model 3D al carcasei si al PCB-ului
2025-03-28 Adaugare mod de utilizare al pinilor ESP32 C6
2025-04-01 Adaugare gerbers.zip
2025-04-02 Adaugare BOM si CPL
2025-04-02 Rezolvare extensie pentru BOM
2025-04-02 Schimbare BOM varianta succinta in README
2025-04-02 Adaugare fisier 3D Fusion 360 cu intreg dispozitivul
2025-04-02 Grupare fisiere
2025-04-03 Schimbare poze model 3D
2025-04-03 Modificari model 3D dispozitiv si PCB
2025-04-04 Modificare erori acceptate
2025-04-08 Imbunatatire diagrama bloc
2025-04-11 Modificare typo in README.md
2025-04-13 Incarcare versiuni finale PCB (2D si 3D)
2025-04-13 Restructurare finala fisiere
2025-04-13 Adaugare modele noi butoane si rezolvare problema schematic
2025-04-13 Imbunatatire README.md
    Adaugare surse externe pentru modelele 3D, precum si actualizarea pozei cu noul PCB 3D

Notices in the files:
parts and their libraries:
COPYRIGHT: Copyright (C) 2024 Ultra Librarian. All rights reserved.
